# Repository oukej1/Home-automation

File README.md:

# Home-automation
Repository for home automation design, and codes.

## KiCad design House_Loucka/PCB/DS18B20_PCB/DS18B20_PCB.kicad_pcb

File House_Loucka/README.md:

Folder for preparation of arduino and RPI based home automation for house in Loučka.

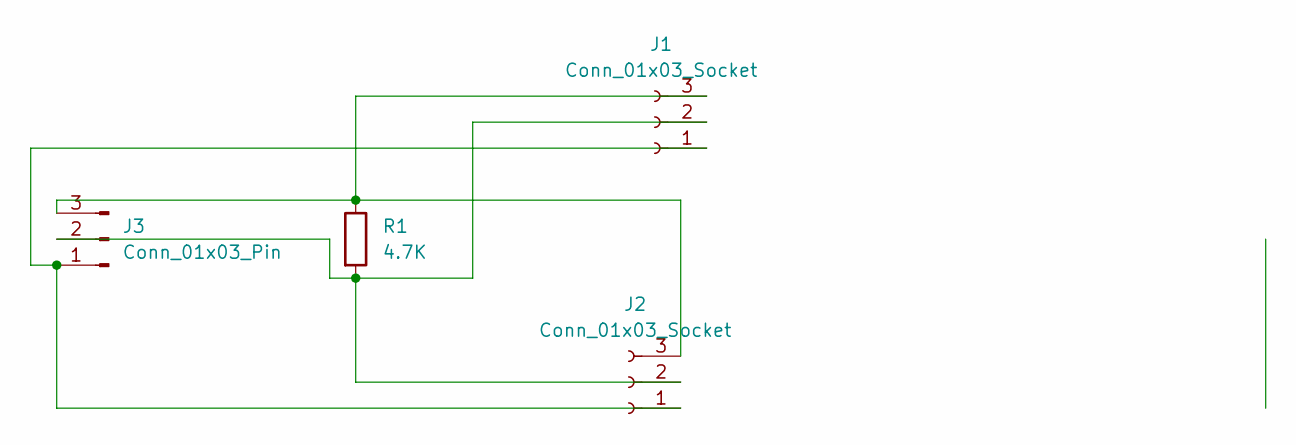
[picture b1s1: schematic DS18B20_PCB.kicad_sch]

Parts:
J1, J2: Conn_01x03_Socket; PinSocket_1x03_P2.54mm_Vertical_SMD_Pin1Left
J3: Conn_01x03_Pin; PinSocket_1x03_P2.54mm_Vertical_SMD_Pin1Right
R1: 4.7K; R_0201_0603Metric

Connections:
unnamed: J1.1, J2.1, J3.1
unnamed: J1.2, J2.2, J3.2, R1.2
unnamed: J1.3, J2.3, J3.3, R1.1

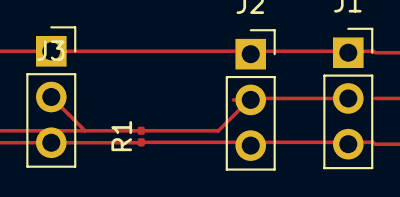
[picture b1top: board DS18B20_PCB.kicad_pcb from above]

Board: 2 copper layers, 4 parts (0 on the bottom side), 3 nets.

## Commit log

2024-04-29 Adding of original file with sensor list
2024-04-29 Creation of folders for Loučka and Hůrka
2024-04-29 Adding of CO2 sensors scenarion, creation of sheets in Rozpis_materialu.ods for lights, sockets, shutters
2024-04-30 odstranění senzorů CO2 z koupelen, přidání jednoho TSL ven na fasádu
2024-05-06 Adding of data cables calculation
2024-05-07 file with cable prices added
2024-05-07 reference in file cabely added for sockets
2024-05-08 Harmonization of file Rozpis_materialu.ods
2024-05-08 fix of rozpis materialu ods
2024-05-08 fix Rozpis_materialu.ods
2024-05-28 Added drawing of 1NP layout
2024-05-28 Ligths added to scheme 1NP
2024-05-28 Lights added to layout 1NP_ELI.drawio
2024-05-28 buttons added to 1NP_ELI.drawio
2024-05-28 Update 1NP_ELI.drawio - PIR sensors added
2024-05-28 Update 1NP_ELI.drawio - temperature sensors added
2024-05-28 Update 1NP_ELI.drawio - heating added
2024-05-28 Update 1NP_ELI.drawio - Heater added to room 111
2024-05-28 Update 1NP_ELI.drawio legend exteded by radiator
2024-06-27 Pridany zasuvky 1NP
2024-06-27 Zásuvky - 1NP komplet
2024-06-27 Oprava - barvy
2024-06-27 Světla úprava
2024-06-27 Oprava barev zasuvky
2024-06-27 Oprava zásuvek
2024-06-27 Přidán LAN
2024-06-27 Přidán videovrátný a dešťovka
2024-06-27 Pridana tabulka Eli_tabulky.ods
2024-06-27 Korekce
2024-06-27 Added 2NP_ELI.drawio
2024-06-27 Pozadi 2NP_ELI.drawio
2024-07-23 External light sensors added
2024-07-23 Lights added
2024-07-23 Lights_complete
2024-07-23 SensorsAdded
2024-07-23 Sensor external added
2024-07-23 Heating added
2024-08-08 Přidány střešní vpusti 1NP_ELI.drawio
2024-08-08 Upraveny přívody podlahového topení1NP_ELI.drawio
2024-08-08 Sock - studna- dešt1NP_ELI.drawio
2024-08-08 Pridany zasuvky 2NP_ELI.drawio
2024-08-08 ZasuvkyHotove 2NP_ELI.drawio
2024-08-08 DatoveZasuvky 2NP_ELI.drawio
2024-08-08 ShuttersComplete 2NP_ELI.drawio
2024-08-08 PridanoStineni_ELI.drawio
2024-08-08 PrecislovanyZasuvky 1NP_ELI.drawio
2024-08-08 2NP added
2024-08-17 PridanoAP 1NP_ELI.drawio
2024-08-17 Přidáno AP 2NP_ELI.drawio
2024-08-17 SoundAdded
2024-08-17 SoundCompleted
2024-08-17 SoundCompleted2NP_ELI.drawio
2024-08-17 soundcomplete
2024-08-17 Sound_adjusted
2024-08-17 SoundUpdate
2024-08-17 Sound and missing items added
2024-08-19 SocketsRenumbered 1NP_ELI.drawio
2024-08-19 Precislovani zasuvek
2024-08-21 FVE_added 1NP_ELI.drawio
2024-08-21 přidána FVE
2024-12-14 Slouceni L1024, Precislovani vse nasledujici o 1 mensi presunuti vypanace B1022 a B1023, Zmena vypinace B1025
2024-12-14 Fix of kitchen in ELI tabulky
2024-12-14 Oprava 1052
2024-12-17 Aktualizovat 1NP_ELI.drawio
2025-01-08 Added Arduino to lights
2025-01-26 Aktualizovat 1NP_ELI.drawio -zásuvky - 101 hala přidáno do okruhu 109, zrušení 1093 a přečíslování všech v 109
2025-01-26 Aktualizovat 1NP_ELI.drawio - zásuvky v obýváku změněny na 101, přečíslování 101 a 100
2025-01-26 Aktualizovat 1NP_ELI.drawio v koupelně přidáno S113-3
2025-01-27 Aktualizovat 1NP_ELI.drawio - zamknutí výkresů
2025-01-27 Přidána složka Rozvadece
2025-02-01 Aktualizovat 1NP_ELI.drawio - updated shutters in room 102
2025-02-01 Aktualizovat 1NP_ELI.drawio S100-3 switched to S109-8
2025-02-01 Aktualizovat 1NP_ELI.drawio - Added B1041, change buttones in 101
2025-02-10 Předelání místnosti 201 - světla
2025-02-10 Aktualizovat 2NP_ELI.drawio
2025-02-10 Aktualizovat 2NP_ELI.drawio oprava Lan barev
2025-02-10 Aktualizovat 2NP_ELI.drawio oprava zásuvek
2025-02-10 Aktualizovat 2NP_ELI.drawio Přidány senzory dveří
2025-02-10 Aktualizovat 1NP_ELI.drawio přidány senzory dveří
2025-02-18 DS18B20 - pcb folder added
2025-02-18 Rozvaděče převedeny na dxf
2025-02-27 Vytvořen soubor Vypocet_slaboproudy_Rozvadec.ods a aktualizace rozvodů
2025-03-08 Kicad PCB files created
2025-03-08 Sync of files between locations
2025-03-27 Přidáno: SchemaRozvadecu.drawio
2025-03-27 Aktualizovat SchemaRozvadecu.drawio
2025-03-27 Update PCB DS18B20 tables updated
2025-03-27 Update tabulek
2025-03-27 Auto stash before merge of "main" and "origin/main"
2025-03-27 Tabulky
2025-03-27 Vytvorena slozka sit
2025-03-27 PridanaTopologieSite
2025-03-27 Aktualizovat Diagram bez názvu.drawio
2025-05-12 Aktualizovat 1NP_ELI.drawio_revizeTlacitek
2025-05-12 Aktualizovat 2NP_ELI.drawio - revize tlačítek světel
2025-06-03 Aktualizovat 1NP_ELI.drawio - odstraněn L1012 na stěně
2025-06-03 Aktualizovat 2NP_ELI.drawio - l1013 přejmenován na L1012
2025-11-07 Přidáno: Diagram bez názvu.drawio
2026-01-06 Přidáno: SlaboproudRozvadec.drawio
